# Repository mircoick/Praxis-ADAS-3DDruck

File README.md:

# Praxissemester: Machbarkeitsanalyse zum System-Update eines 3D-Industriedruckers

In diesem Repository ist die technische und wirtschaftliche Machbarkeit eines System-Updates (Hardware & Software) für den 3D-Industriedrucker **3Dgence INDUSTRY F421** dokumentiert. Im Rahmen des Praxissemesters bei der **Airbus DS Airborne Solutions GmbH** wurde die Migration auf moderne Open-Source-Komponenten untersucht.

---

## Dokumentation & Berichte

Die offiziellen Berichte und Ausarbeitungen stehen im PDF-Format zur Verfügung:
* [Zwischenbericht (PDF)](report/.output/Zwischenbericht_Mirco_Ick_5312533.pdf)
* [Abschlussbericht (PDF)](report/.output/prx_final_report.pdf)

---

## Repository-Struktur

Das Repository gliedert sich in folgende Hauptkomponenten:

<table>
  <thead>
    <tr>
      <th>Verzeichnis</th>
      <th>Beschreibung</th>
    </tr>
  </thead>
  <tbody>
    <tr>
      <td><a href="doku/"><code>doku/</code></a></td>
      <td>Ergänzende Projektdokumentationen.</td>
    </tr>
    <tr>
      <td><a href="info/"><code>info/</code></a></td>
      <td>Datenblätter und Firmeninfos.</td>
    </tr>
    <tr>
      <td><a href="kicad/"><code>kicad/</code></a></td>
      <td>Idee einer Adapterplatine mit Schaltplänen.</td>
    </tr>
    <tr>
      <td><a href="klipper/"><code>klipper/</code></a></td>
      <td>Konfigurationsdateien, Makros und Firmware-Anpassungen für Klipper.</td>
    </tr>
    <tr>
      <td><a href="print_data/"><code>print_data/</code></a></td>
      <td>Testdrucke, Slicer-Profile und druckspezifische Daten.</td>
    </tr>
    <tr>
      <td><a href="python/"><code>python/</code></a></td>
      <td>Skripte zur isolierten Sensor- und Hardware-Ansteuerung.</td>
    </tr>
    <tr>
      <td><a href="report/"><code>report/</code></a></td>
      <td>Quarto-Quellcode (<code>.qmd</code>) und Build-Artefakte der Berichte.</td>
    </tr>
  </tbody>
</table>

---

## 🛠️ Systemdaten & Key Facts

* **Hersteller:** 3Dgence
* **Modell:** INDUSTRY F421
* **Kernziele:** Evaluierung neuer Steuerungs-Hardware (u. a. Mainboard- und Sensor-Integration), Firmware-Umstellung auf Klipper sowie Analyse der technischen und wirtschaftlichen Realisierbarkeit.

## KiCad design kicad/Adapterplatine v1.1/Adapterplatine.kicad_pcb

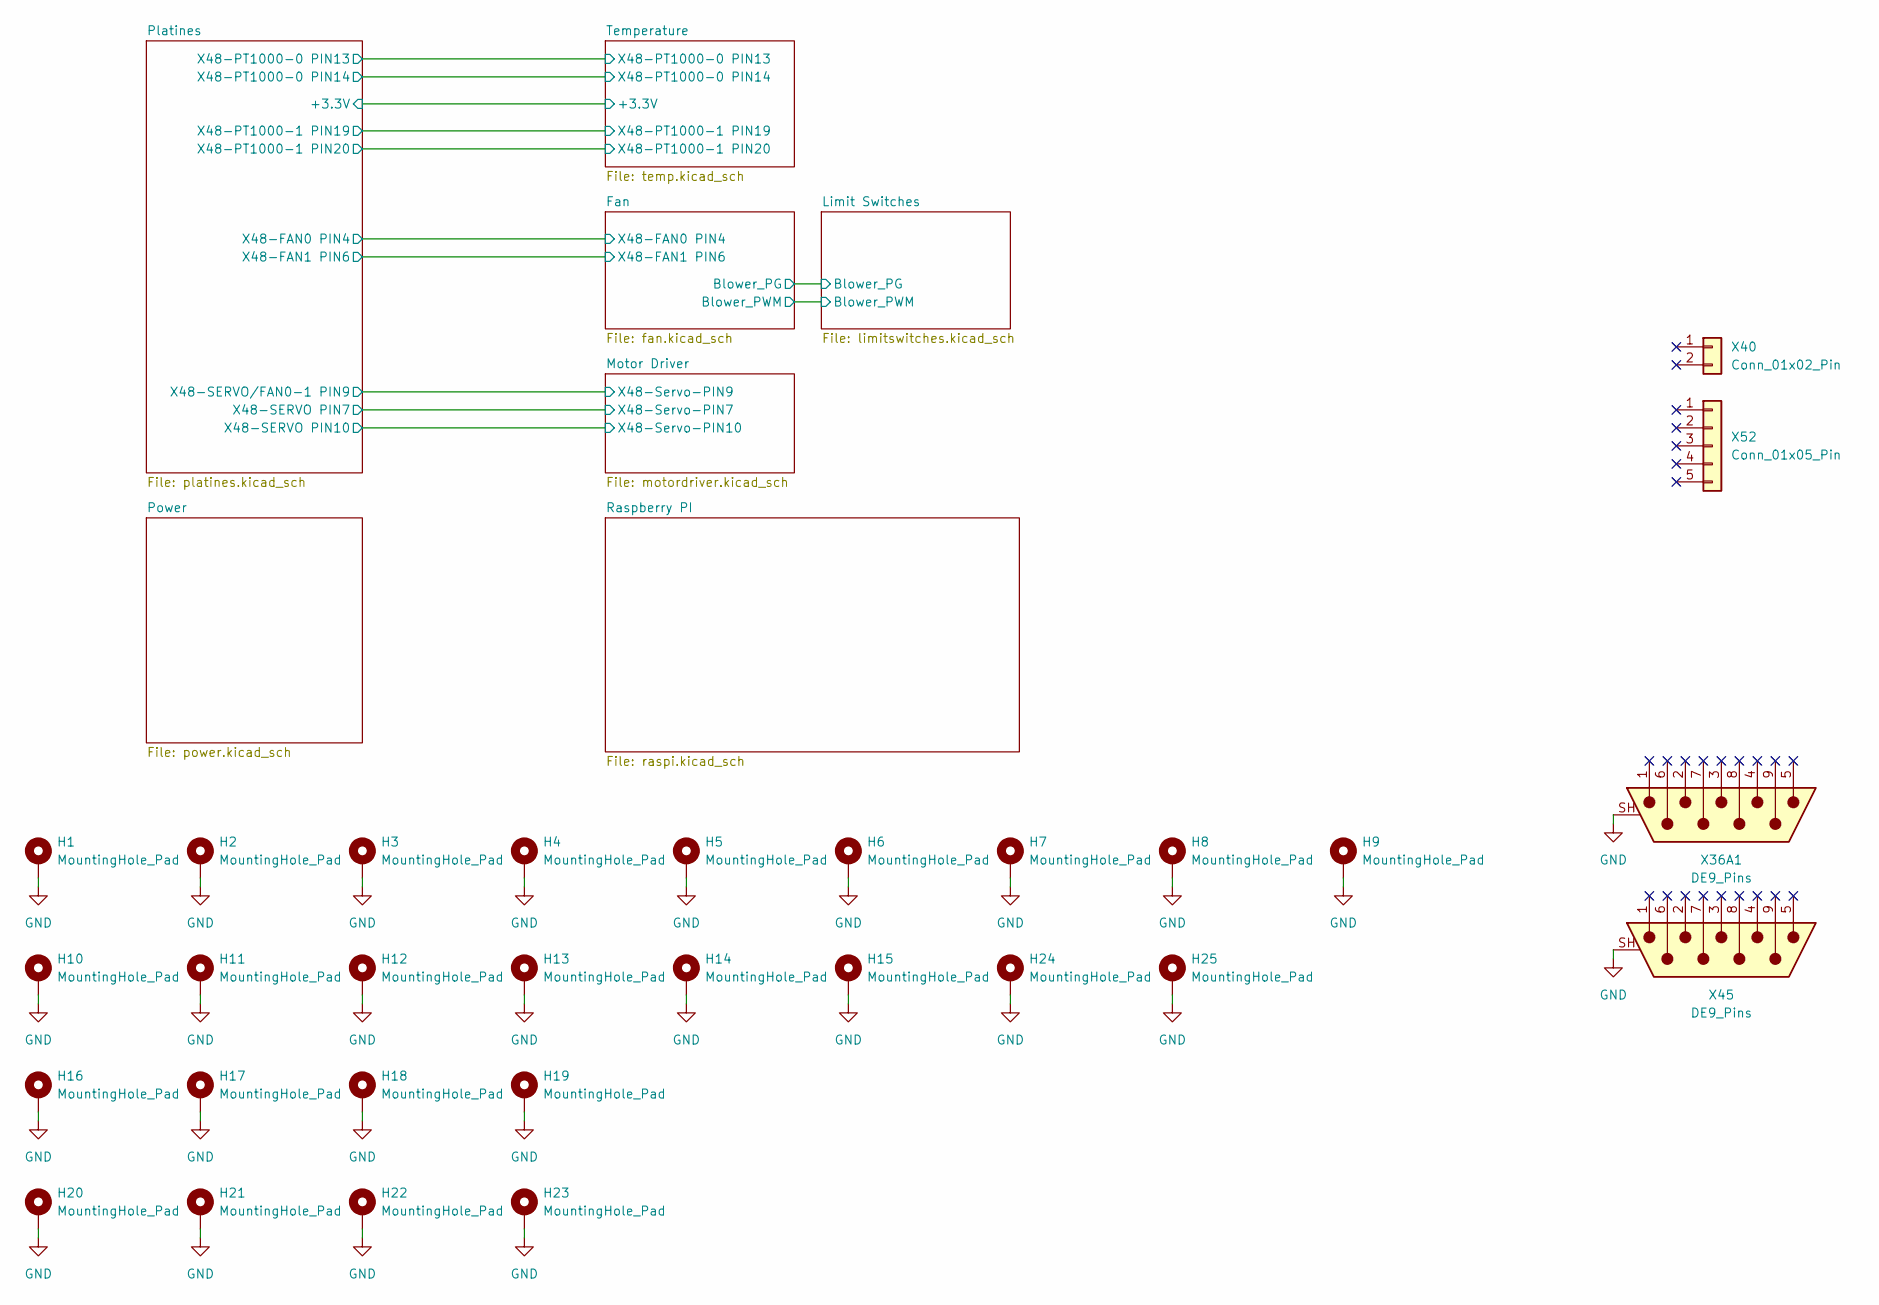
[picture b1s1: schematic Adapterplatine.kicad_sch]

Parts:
H1, H2, H3, H4, H5, H6, H7, H8, H9, H10, H11, H12, H13, H14, H15, H24, H25: MountingHole_Pad; MountingHole_3.5mm_Pad
H16, H17, H18, H19, H20, H21, H22, H23: MountingHole_Pad; MountingHole_3.5mm_Pad_Via_10mm_Aufbau
X36A1, X45: DE9_Pins; DSUB-9_Pins_Vertical_P2.77x2.84mm_MountingHoles
X40: Conn_01x02_Pin; PinHeader_1x02_P2.54mm_Vertical
X52: Conn_01x05_Pin; PinHeader_1x05_P2.54mm_Vertical

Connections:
GND: H1.1 (1_1), H2.1 (1_1), H3.1 (1_1), H4.1 (1_1), H5.1 (1_1), H6.1 (1_1), H7.1 (1_1), H8.1 (1_1), H9.1 (1_1), H10.1 (1_1), H11.1 (1_1), H12.1 (1_1), H13.1 (1_1), H14.1 (1_1), H15.1 (1_1), H16.1 (1_1), H17.1 (1_1), H18.1 (1_1), H19.1 (1_1), H20.1 (1_1), H21.1 (1_1), H22.1 (1_1), H23.1 (1_1), H24.1 (1_1), H25.1 (1_1), X36A1.SH (PAD_SH), X45.SH (PAD_SH); also elsewhere on the board

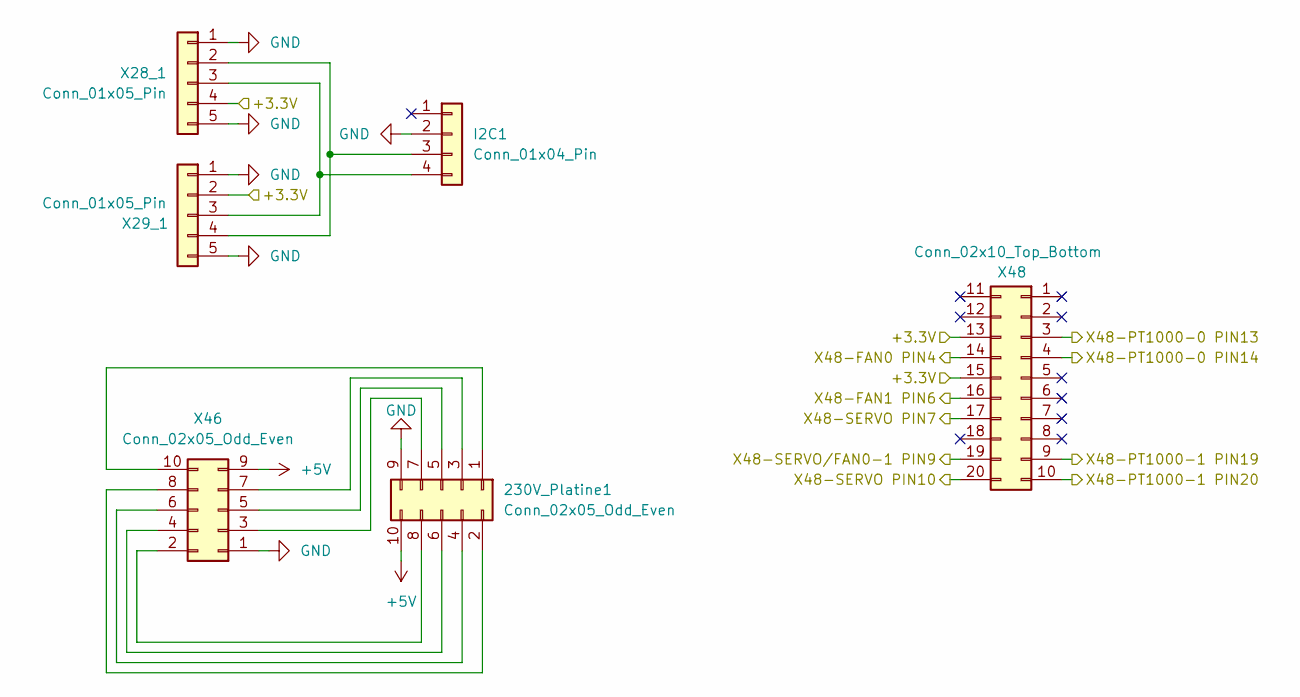
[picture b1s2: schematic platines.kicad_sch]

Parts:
230V_Platine1: Conn_02x05_Odd_Even; IDC-Header_2x05_P2.54mm_Vertical
I2C1: Conn_01x04_Pin; PinHeader_1x04_P2.54mm_Vertical
X28_1, X29_1: Conn_01x05_Pin; PinHeader_1x05_P2.54mm_Vertical
X46: Conn_02x05_Odd_Even; IDC-Header_2x05_P2.54mm_Vertical
X48: Conn_02x10_Top_Bottom; Molex_Micro-Fit_3.0_43045-2012_2x10_P3.00mm_Vertical

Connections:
+5V: 230V_Platine1.10, X46.9; also elsewhere on the board
/Fan/X48-FAN0 PIN4: X48.14; also elsewhere on the board
/Fan/X48-FAN1 PIN6: X48.16; also elsewhere on the board
/Motor Driver/X48-Servo-PIN7: X48.17; also elsewhere on the board
/Motor Driver/X48-Servo-PIN9: X48.19; also elsewhere on the board
/Motor Driver/X48-Servo-PIN10: X48.20; also elsewhere on the board
/Platines/+3.3V: X28_1.4, X29_1.2, X48.13, X48.15; also elsewhere on the board
/Platines/X48-PT1000-0 PIN13: X48.3; also elsewhere on the board
/Platines/X48-PT1000-0 PIN14: X48.4; also elsewhere on the board
/Platines/X48-PT1000-1 PIN19: X48.9; also elsewhere on the board
/Platines/X48-PT1000-1 PIN20: X48.10; also elsewhere on the board
GND: 230V_Platine1.9, I2C1.2, X28_1.1, X28_1.5, X29_1.1, X29_1.5, X46.1; also elsewhere on the board
unnamed: 230V_Platine1.1, X46.10
unnamed: 230V_Platine1.2, X46.8
unnamed: 230V_Platine1.3, X46.7
unnamed: 230V_Platine1.4, X46.6
unnamed: 230V_Platine1.5, X46.5
unnamed: 230V_Platine1.6, X46.4
unnamed: 230V_Platine1.7, X46.3
unnamed: 230V_Platine1.8, X46.2
unnamed: I2C1.3, X28_1.2, X29_1.4
unnamed: I2C1.4, X28_1.3, X29_1.3

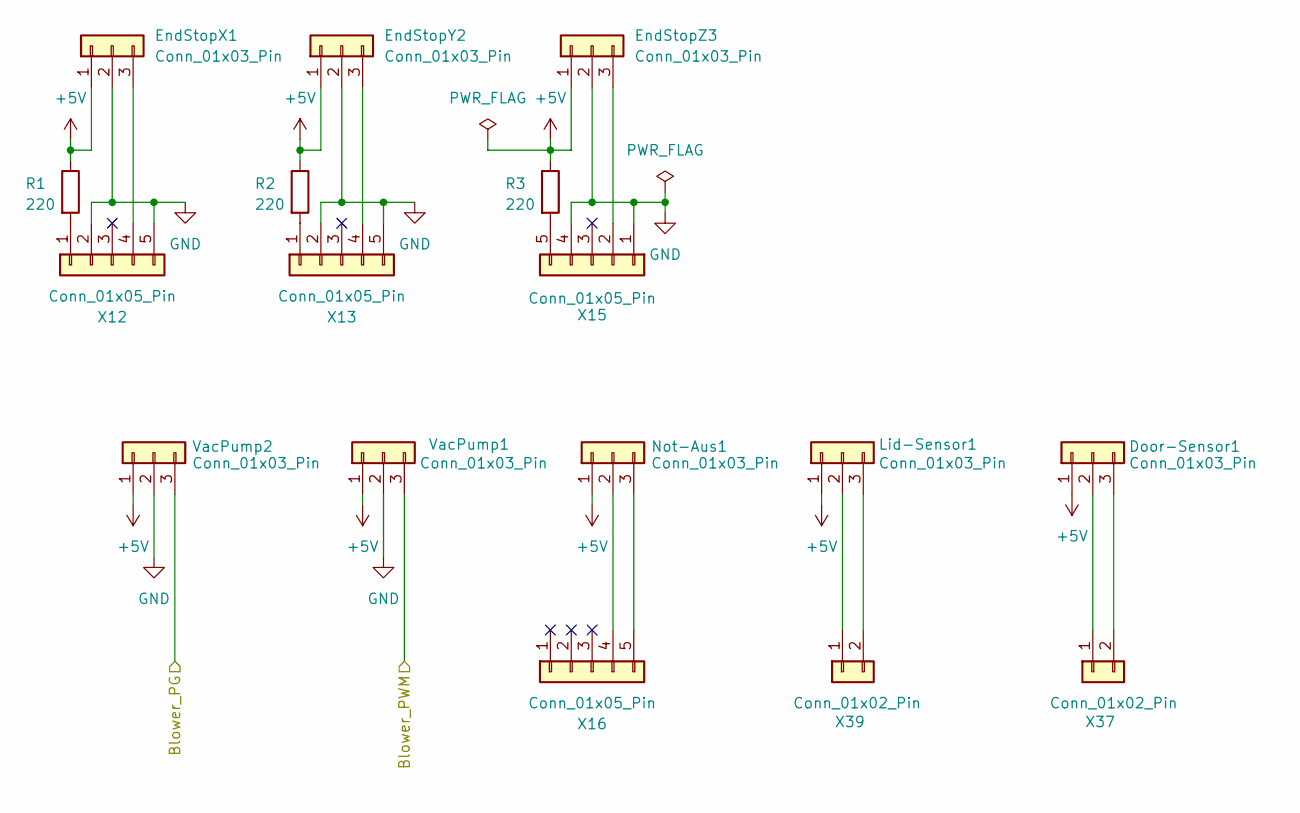
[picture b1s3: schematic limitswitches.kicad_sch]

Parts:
Door-Sensor1: Conn_01x03_Pin; JST_XH_B3B-XH-A_1x03_P2.50mm_Vertical
EndStopX1: Conn_01x03_Pin; JST_XH_B3B-XH-A_1x03_P2.50mm_Vertical
EndStopY2: Conn_01x03_Pin; JST_XH_B3B-XH-A_1x03_P2.50mm_Vertical
EndStopZ3: Conn_01x03_Pin; JST_XH_B3B-XH-A_1x03_P2.50mm_Vertical
Lid-Sensor1: Conn_01x03_Pin; JST_XH_B3B-XH-A_1x03_P2.50mm_Vertical
Not-Aus1: Conn_01x03_Pin; JST_XH_B3B-XH-A_1x03_P2.50mm_Vertical
R1, R2, R3: 220; R_Axial_DIN0207_L6.3mm_D2.5mm_P10.16mm_Horizontal
VacPump1, VacPump2: Conn_01x03_Pin; JST_XH_B3B-XH-A_1x03_P2.50mm_Vertical
X12, X13, X15, X16: Conn_01x05_Pin; PinHeader_1x05_P2.54mm_Vertical
X37, X39: Conn_01x02_Pin; PinHeader_1x02_P2.54mm_Vertical

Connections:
+5V: Door-Sensor1.1, EndStopX1.1, EndStopY2.1, EndStopZ3.1, Lid-Sensor1.1, Not-Aus1.1, R1.1, R2.1, R3.1, VacPump1.1, VacPump2.1; also elsewhere on the board
/Fan/Blower_PG: VacPump2.3; also elsewhere on the board
/Fan/Blower_PWM: VacPump1.3; also elsewhere on the board
GND: EndStopX1.2, EndStopY2.2, EndStopZ3.2, VacPump1.2, VacPump2.2, X12.2, X12.5, X13.2, X13.5, X15.1, X15.4; also elsewhere on the board
unnamed: Door-Sensor1.2, X37.1
unnamed: Door-Sensor1.3, X37.2
unnamed: EndStopX1.3, X12.4
unnamed: EndStopY2.3, X13.4
unnamed: EndStopZ3.3, X15.2
unnamed: Lid-Sensor1.2, X39.1
unnamed: Lid-Sensor1.3, X39.2
unnamed: Not-Aus1.2, X16.4
unnamed: Not-Aus1.3, X16.5
unnamed: R1.2, X12.1
unnamed: R2.2, X13.1
unnamed: R3.2, X15.5

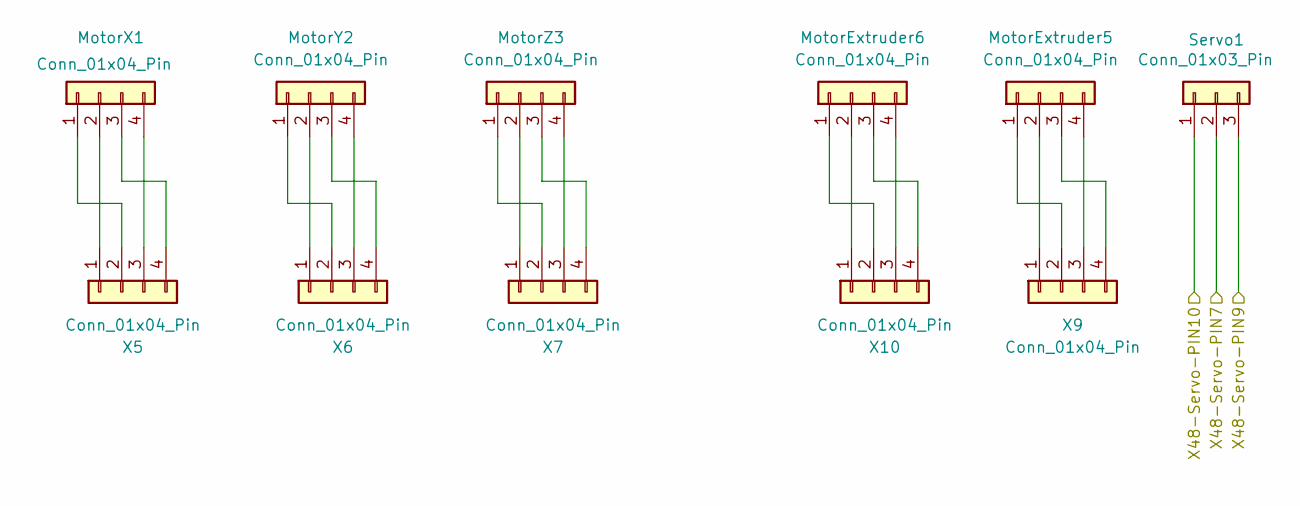
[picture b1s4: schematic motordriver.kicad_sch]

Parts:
MotorExtruder5, MotorExtruder6: Conn_01x04_Pin; JST_XH_B4B-XH-A_1x04_P2.50mm_Vertical
MotorX1: Conn_01x04_Pin; JST_VH_B4P-VH_1x04_P3.96mm_Vertical
MotorY2: Conn_01x04_Pin; JST_VH_B4P-VH_1x04_P3.96mm_Vertical
MotorZ3: Conn_01x04_Pin; JST_VH_B4P-VH_1x04_P3.96mm_Vertical
Servo1: Conn_01x03_Pin; JST_XH_B3B-XH-A_1x03_P2.50mm_Vertical
X5, X6, X7, X9, X10: Conn_01x04_Pin; PhoenixContact_MSTBVA_2,5_4-G-5,08_1x04_P5.08mm_Vertical

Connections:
/Motor Driver/X48-Servo-PIN7: Servo1.2; also elsewhere on the board
/Motor Driver/X48-Servo-PIN9: Servo1.3; also elsewhere on the board
/Motor Driver/X48-Servo-PIN10: Servo1.1; also elsewhere on the board
unnamed: MotorExtruder5.1, X9.2
unnamed: MotorExtruder5.2, X9.1
unnamed: MotorExtruder5.3, X9.4
unnamed: MotorExtruder5.4, X9.3
unnamed: MotorExtruder6.1, X10.2
unnamed: MotorExtruder6.2, X10.1
unnamed: MotorExtruder6.3, X10.4
unnamed: MotorExtruder6.4, X10.3
unnamed: MotorX1.1, X5.2
unnamed: MotorX1.2, X5.1
unnamed: MotorX1.3, X5.4
unnamed: MotorX1.4, X5.3
unnamed: MotorY2.1, X6.2
unnamed: MotorY2.2, X6.1
unnamed: MotorY2.3, X6.4
unnamed: MotorY2.4, X6.3
unnamed: MotorZ3.1, X7.2
unnamed: MotorZ3.2, X7.1
unnamed: MotorZ3.3, X7.4
unnamed: MotorZ3.4, X7.3

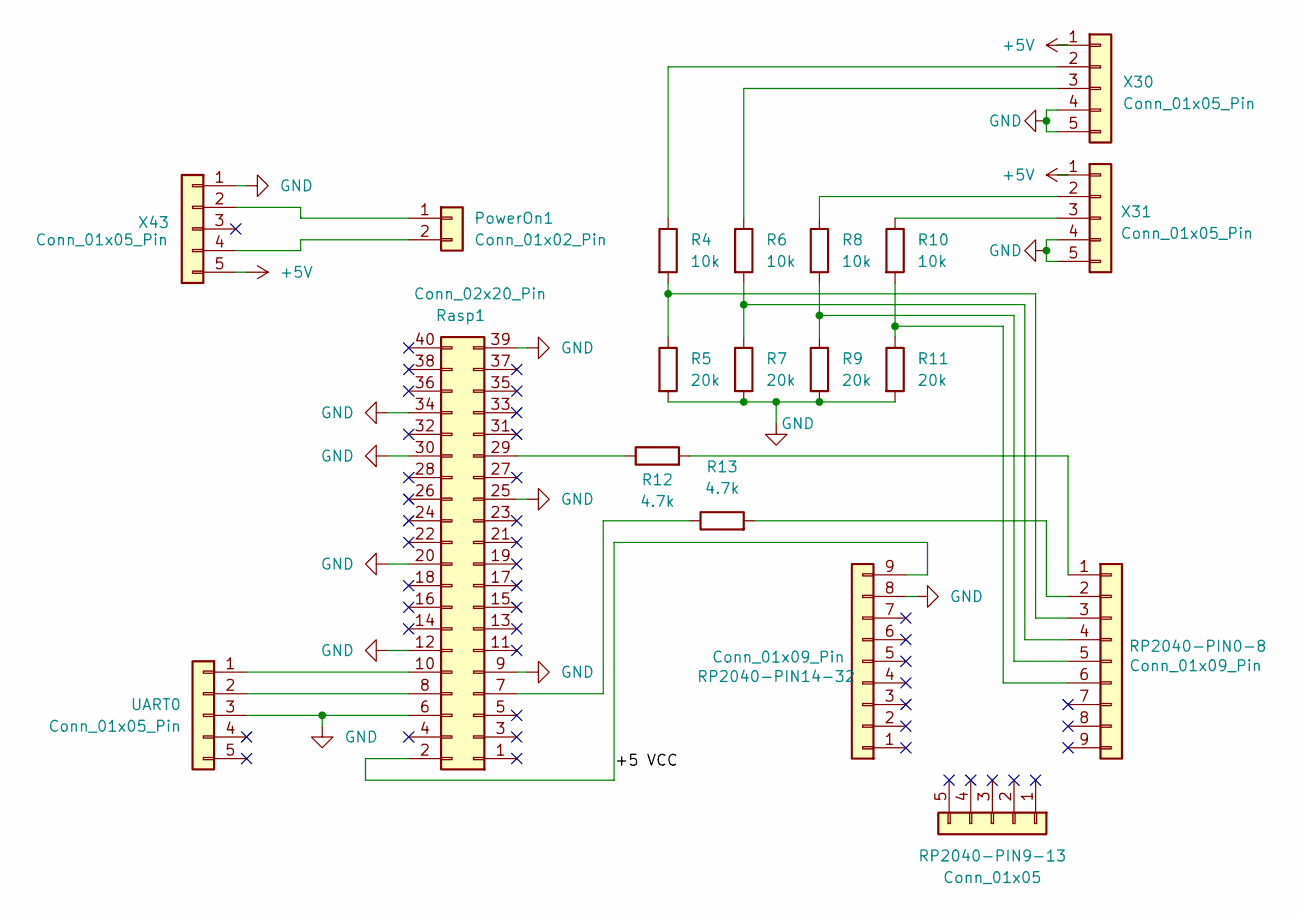
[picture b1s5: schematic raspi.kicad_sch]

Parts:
PowerOn1: Conn_01x02_Pin; PinHeader_1x02_P2.54mm_Vertical
R4, R6, R8, R10: 10k; R_Axial_DIN0207_L6.3mm_D2.5mm_P10.16mm_Horizontal
R5, R7, R9, R11: 20k; R_Axial_DIN0207_L6.3mm_D2.5mm_P10.16mm_Horizontal
R12, R13: 4.7k; R_Axial_DIN0207_L6.3mm_D2.5mm_P10.16mm_Horizontal
RP2040-PIN0-8, RP2040-PIN14-32: Conn_01x09_Pin; PinSocket_1x09_P2.54mm_Vertical
RP2040-PIN9-13: Conn_01x05; PinSocket_1x05_P2.54mm_Vertical
Rasp1: Conn_02x20_Pin; IDC-Header_2x20_P2.54mm_Vertical
UART0: Conn_01x05_Pin; PinHeader_1x05_P2.54mm_Vertical
X30, X31, X43: Conn_01x05_Pin; PinHeader_1x05_P2.54mm_Vertical

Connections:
+5V: X30.1, X31.1, X43.5; also elsewhere on the board
/Raspberry PI/+5 VCC: RP2040-PIN14-32.9, Rasp1.2
GND: R5.2, R7.2, R9.2, R11.2, RP2040-PIN14-32.8, Rasp1.6, Rasp1.9, Rasp1.12, Rasp1.20, Rasp1.25, Rasp1.30, Rasp1.34, Rasp1.39, UART0.3, X30.4, X30.5, X31.4, X31.5, X43.1; also elsewhere on the board
unnamed: PowerOn1.1, X43.2
unnamed: PowerOn1.2, X43.4
unnamed: R12.2, RP2040-PIN0-8.1
unnamed: R13.2, RP2040-PIN0-8.2
unnamed: R4.2, R5.1, RP2040-PIN0-8.3
unnamed: R6.2, R7.1, RP2040-PIN0-8.4
unnamed: R8.2, R9.1, RP2040-PIN0-8.5
unnamed: R10.2, R11.1, RP2040-PIN0-8.6
unnamed: R13.1, Rasp1.7
unnamed: Rasp1.8, UART0.2
unnamed: Rasp1.10, UART0.1
unnamed: R12.1, Rasp1.29
unnamed: R4.1, X30.2
unnamed: R6.1, X30.3
unnamed: R8.1, X31.2
unnamed: R10.1, X31.3

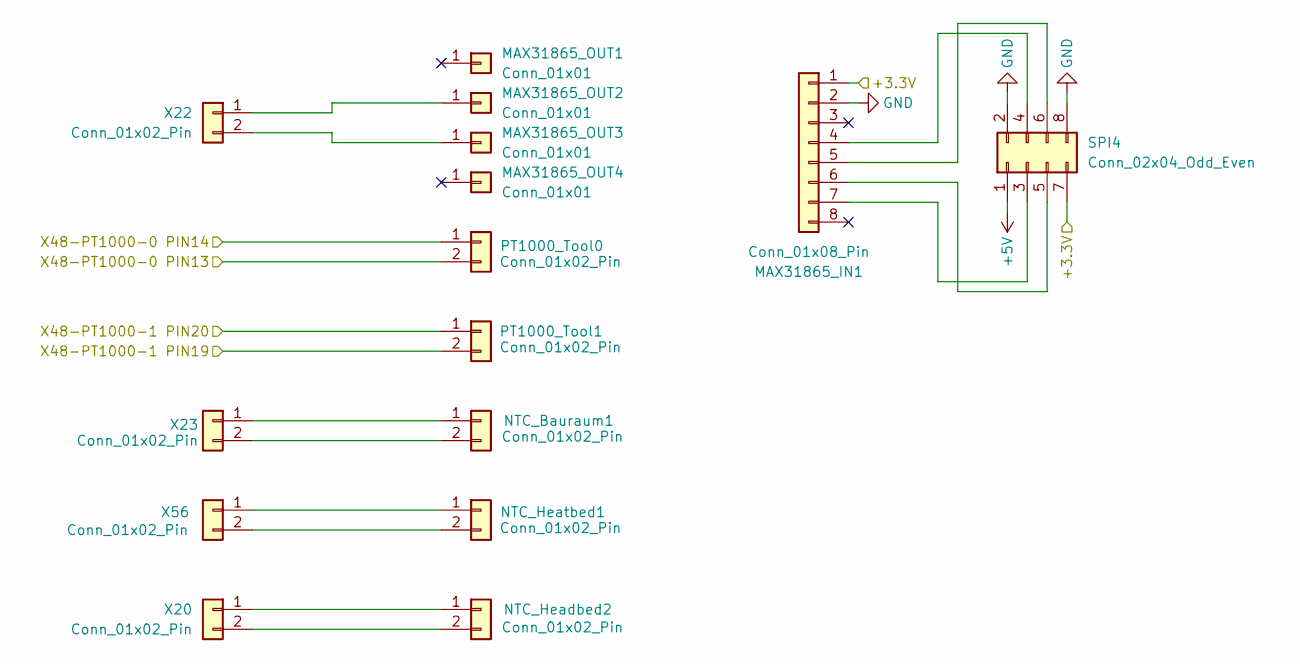
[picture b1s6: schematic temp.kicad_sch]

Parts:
MAX31865_IN1: Conn_01x08_Pin; PinSocket_1x08_P2.54mm_Vertical
MAX31865_OUT1, MAX31865_OUT2, MAX31865_OUT3, MAX31865_OUT4: Conn_01x01; PinSocket_1x01_P2.54mm_Vertical
NTC_Bauraum1: Conn_01x02_Pin; JST_XH_B2B-XH-A_1x02_P2.50mm_Vertical
NTC_Headbed2: Conn_01x02_Pin; JST_XH_B2B-XH-A_1x02_P2.50mm_Vertical
NTC_Heatbed1: Conn_01x02_Pin; JST_XH_B2B-XH-A_1x02_P2.50mm_Vertical
PT1000_Tool0, PT1000_Tool1: Conn_01x02_Pin; JST_XH_B2B-XH-A_1x02_P2.50mm_Vertical
SPI4: Conn_02x04_Odd_Even; PinHeader_2x04_P2.54mm_Vertical
X20, X22, X23, X56: Conn_01x02_Pin; PinHeader_1x02_P2.54mm_Vertical

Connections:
+5V: SPI4.1; also elsewhere on the board
/Platines/+3.3V: MAX31865_IN1.1, SPI4.7; also elsewhere on the board
/Platines/X48-PT1000-0 PIN13: PT1000_Tool0.2; also elsewhere on the board
/Platines/X48-PT1000-0 PIN14: PT1000_Tool0.1; also elsewhere on the board
/Platines/X48-PT1000-1 PIN19: PT1000_Tool1.2; also elsewhere on the board
/Platines/X48-PT1000-1 PIN20: PT1000_Tool1.1; also elsewhere on the board
GND: MAX31865_IN1.2, SPI4.2, SPI4.8; also elsewhere on the board
unnamed: MAX31865_IN1.4, SPI4.4
unnamed: MAX31865_IN1.5, SPI4.6
unnamed: MAX31865_IN1.6, SPI4.5
unnamed: MAX31865_IN1.7, SPI4.3
unnamed: MAX31865_OUT2.1 (Pin_1_1), X22.1
unnamed: MAX31865_OUT3.1 (Pin_1_1), X22.2
unnamed: NTC_Bauraum1.1, X23.1
unnamed: NTC_Bauraum1.2, X23.2
unnamed: NTC_Headbed2.1, X20.1
unnamed: NTC_Headbed2.2, X20.2
unnamed: NTC_Heatbed1.1, X56.1
unnamed: NTC_Heatbed1.2, X56.2

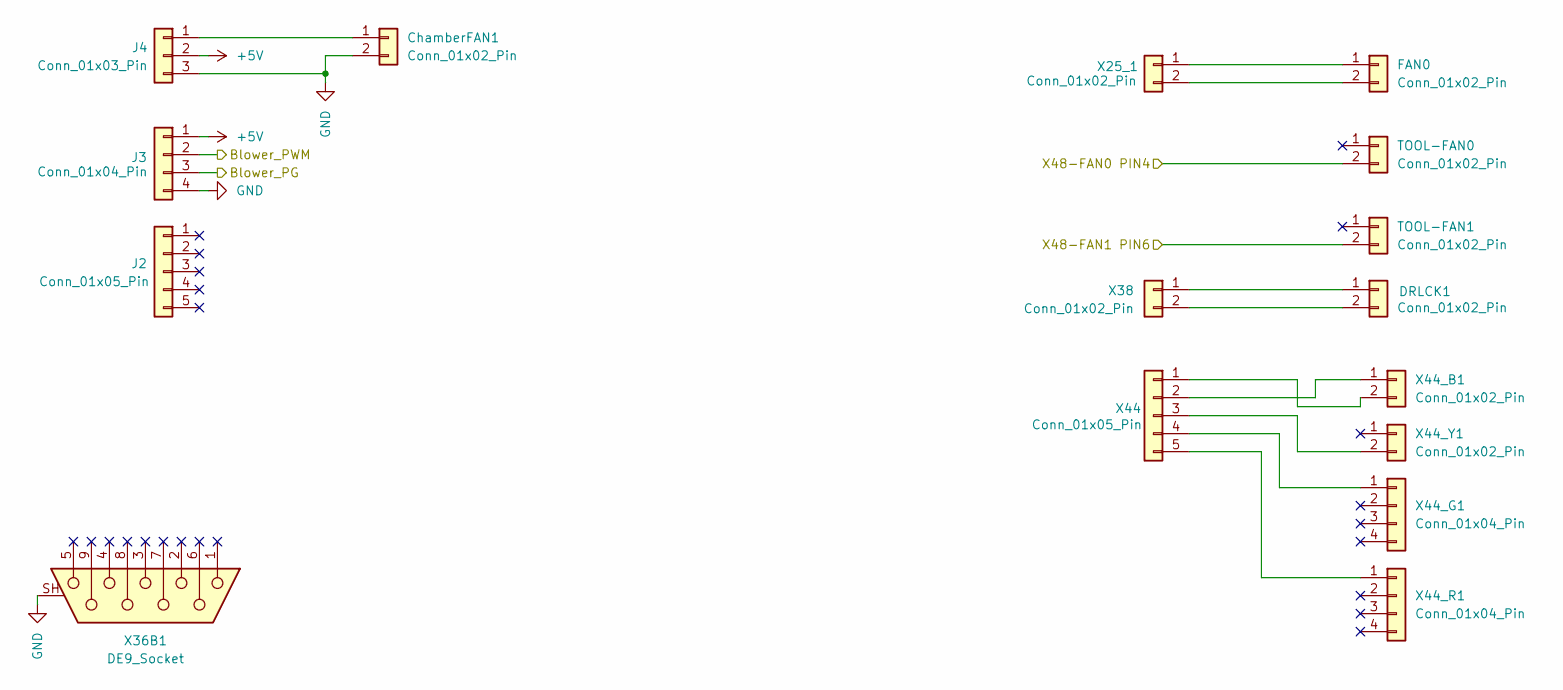
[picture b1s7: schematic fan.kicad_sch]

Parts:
ChamberFAN1: Conn_01x02_Pin; JST_XH_B2B-XH-A_1x02_P2.50mm_Vertical
DRLCK1: Conn_01x02_Pin; JST_XH_B2B-XH-A_1x02_P2.50mm_Vertical
FAN0: Conn_01x02_Pin; JST_XH_B2B-XH-A_1x02_P2.50mm_Vertical
J2: Conn_01x05_Pin; PinHeader_1x05_P2.54mm_Vertical
J3: Conn_01x04_Pin; PinHeader_1x04_P2.54mm_Vertical
J4: Conn_01x03_Pin; PinHeader_1x03_P2.54mm_Vertical
TOOL-FAN0, TOOL-FAN1: Conn_01x02_Pin; JST_XH_B2B-XH-A_1x02_P2.50mm_Vertical
X25_1, X38: Conn_01x02_Pin; PinHeader_1x02_P2.54mm_Vertical
X36B1: DE9_Socket; DSUB-9_Socket_Vertical_P2.77x2.84mm_MountingHoles
X44: Conn_01x05_Pin; PinHeader_1x05_P2.54mm_Vertical
X44_B1, X44_Y1: Conn_01x02_Pin; JST_XH_B2B-XH-A_1x02_P2.50mm_Vertical
X44_G1, X44_R1: Conn_01x04_Pin; Molex_KK-254_AE-6410-04A_1x04_P2.54mm_Vertical

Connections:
+5V: J3.1, J4.2; also elsewhere on the board
/Fan/Blower_PG: J3.3; also elsewhere on the board
/Fan/Blower_PWM: J3.2; also elsewhere on the board
/Fan/X48-FAN0 PIN4: TOOL-FAN0.2 (Pin_2_2); also elsewhere on the board
/Fan/X48-FAN1 PIN6: TOOL-FAN1.2 (Pin_2_2); also elsewhere on the board
GND: ChamberFAN1.2, J3.4, J4.3, X36B1.SH (PAD_SH); also elsewhere on the board
unnamed: ChamberFAN1.1, J4.1
unnamed: DRLCK1.1, X38.1
unnamed: DRLCK1.2, X38.2
unnamed: FAN0.1, X25_1.1
unnamed: FAN0.2, X25_1.2
unnamed: X44.1, X44_B1.2
unnamed: X44.2, X44_B1.1
unnamed: X44.3, X44_Y1.2 (Pin_2_2)
unnamed: X44.4, X44_G1.1 (Pin_1_1)
unnamed: X44.5, X44_R1.1 (Pin_1_1)

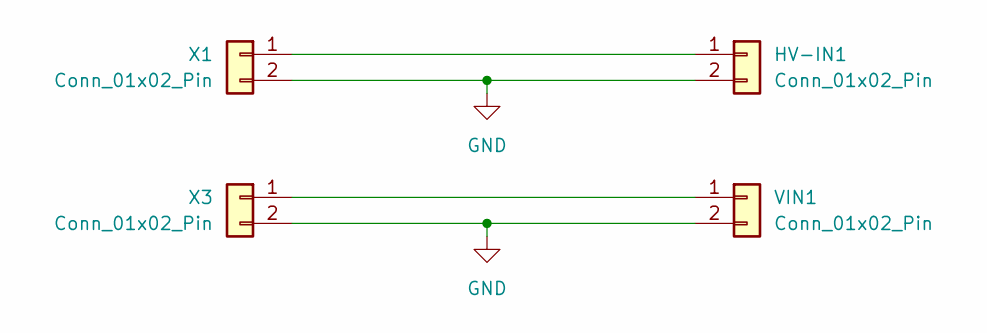
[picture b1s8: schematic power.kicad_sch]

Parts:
HV-IN1: Conn_01x02_Pin; PhoenixContact_MSTBVA_2,5_2-G_1x02_P5.00mm_Vertical
VIN1: Conn_01x02_Pin; PhoenixContact_MSTBVA_2,5_2-G_1x02_P5.00mm_Vertical
X1, X3: Conn_01x02_Pin; PhoenixContact_MSTBA_2,5_2-G_1x02_P5.00mm_Horizontal

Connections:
GND: HV-IN1.2, VIN1.2, X1.2, X3.2; also elsewhere on the board
unnamed: HV-IN1.1, X1.1
unnamed: VIN1.1, X3.1

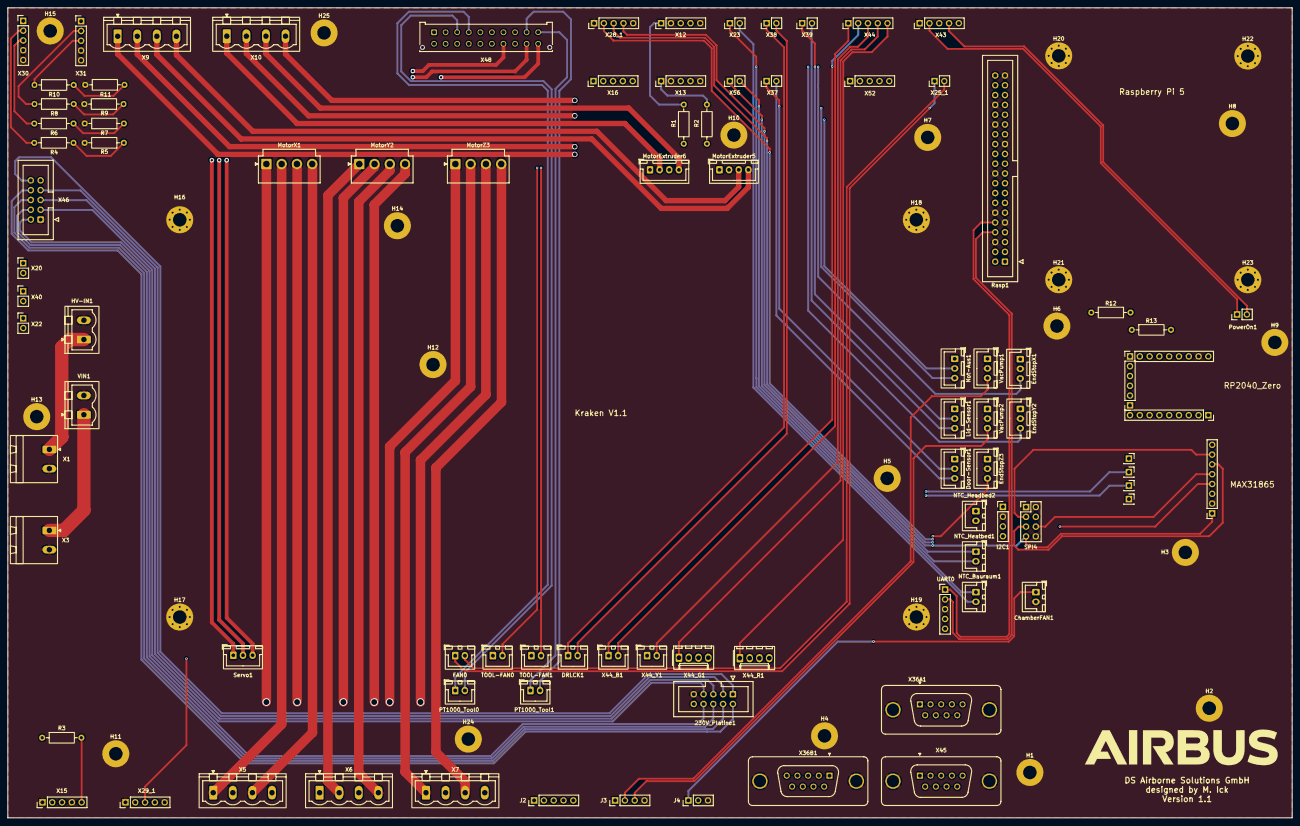
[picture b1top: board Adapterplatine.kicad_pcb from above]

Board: 4 copper layers, 333.0 x 210.0 mm, 122 parts (0 on the bottom side), 97 nets.

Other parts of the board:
AirbusLogo: LOGO; Airbus
Kraken V1.1: Kraken V1.1
MAX31865: MAX31865
RP2040_Zero: RP2040
Raspberry Pi 5: Raspberry Pi 5
